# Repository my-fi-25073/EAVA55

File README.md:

# EAVA55
EAVA55 pcb &amp; qmk firmware

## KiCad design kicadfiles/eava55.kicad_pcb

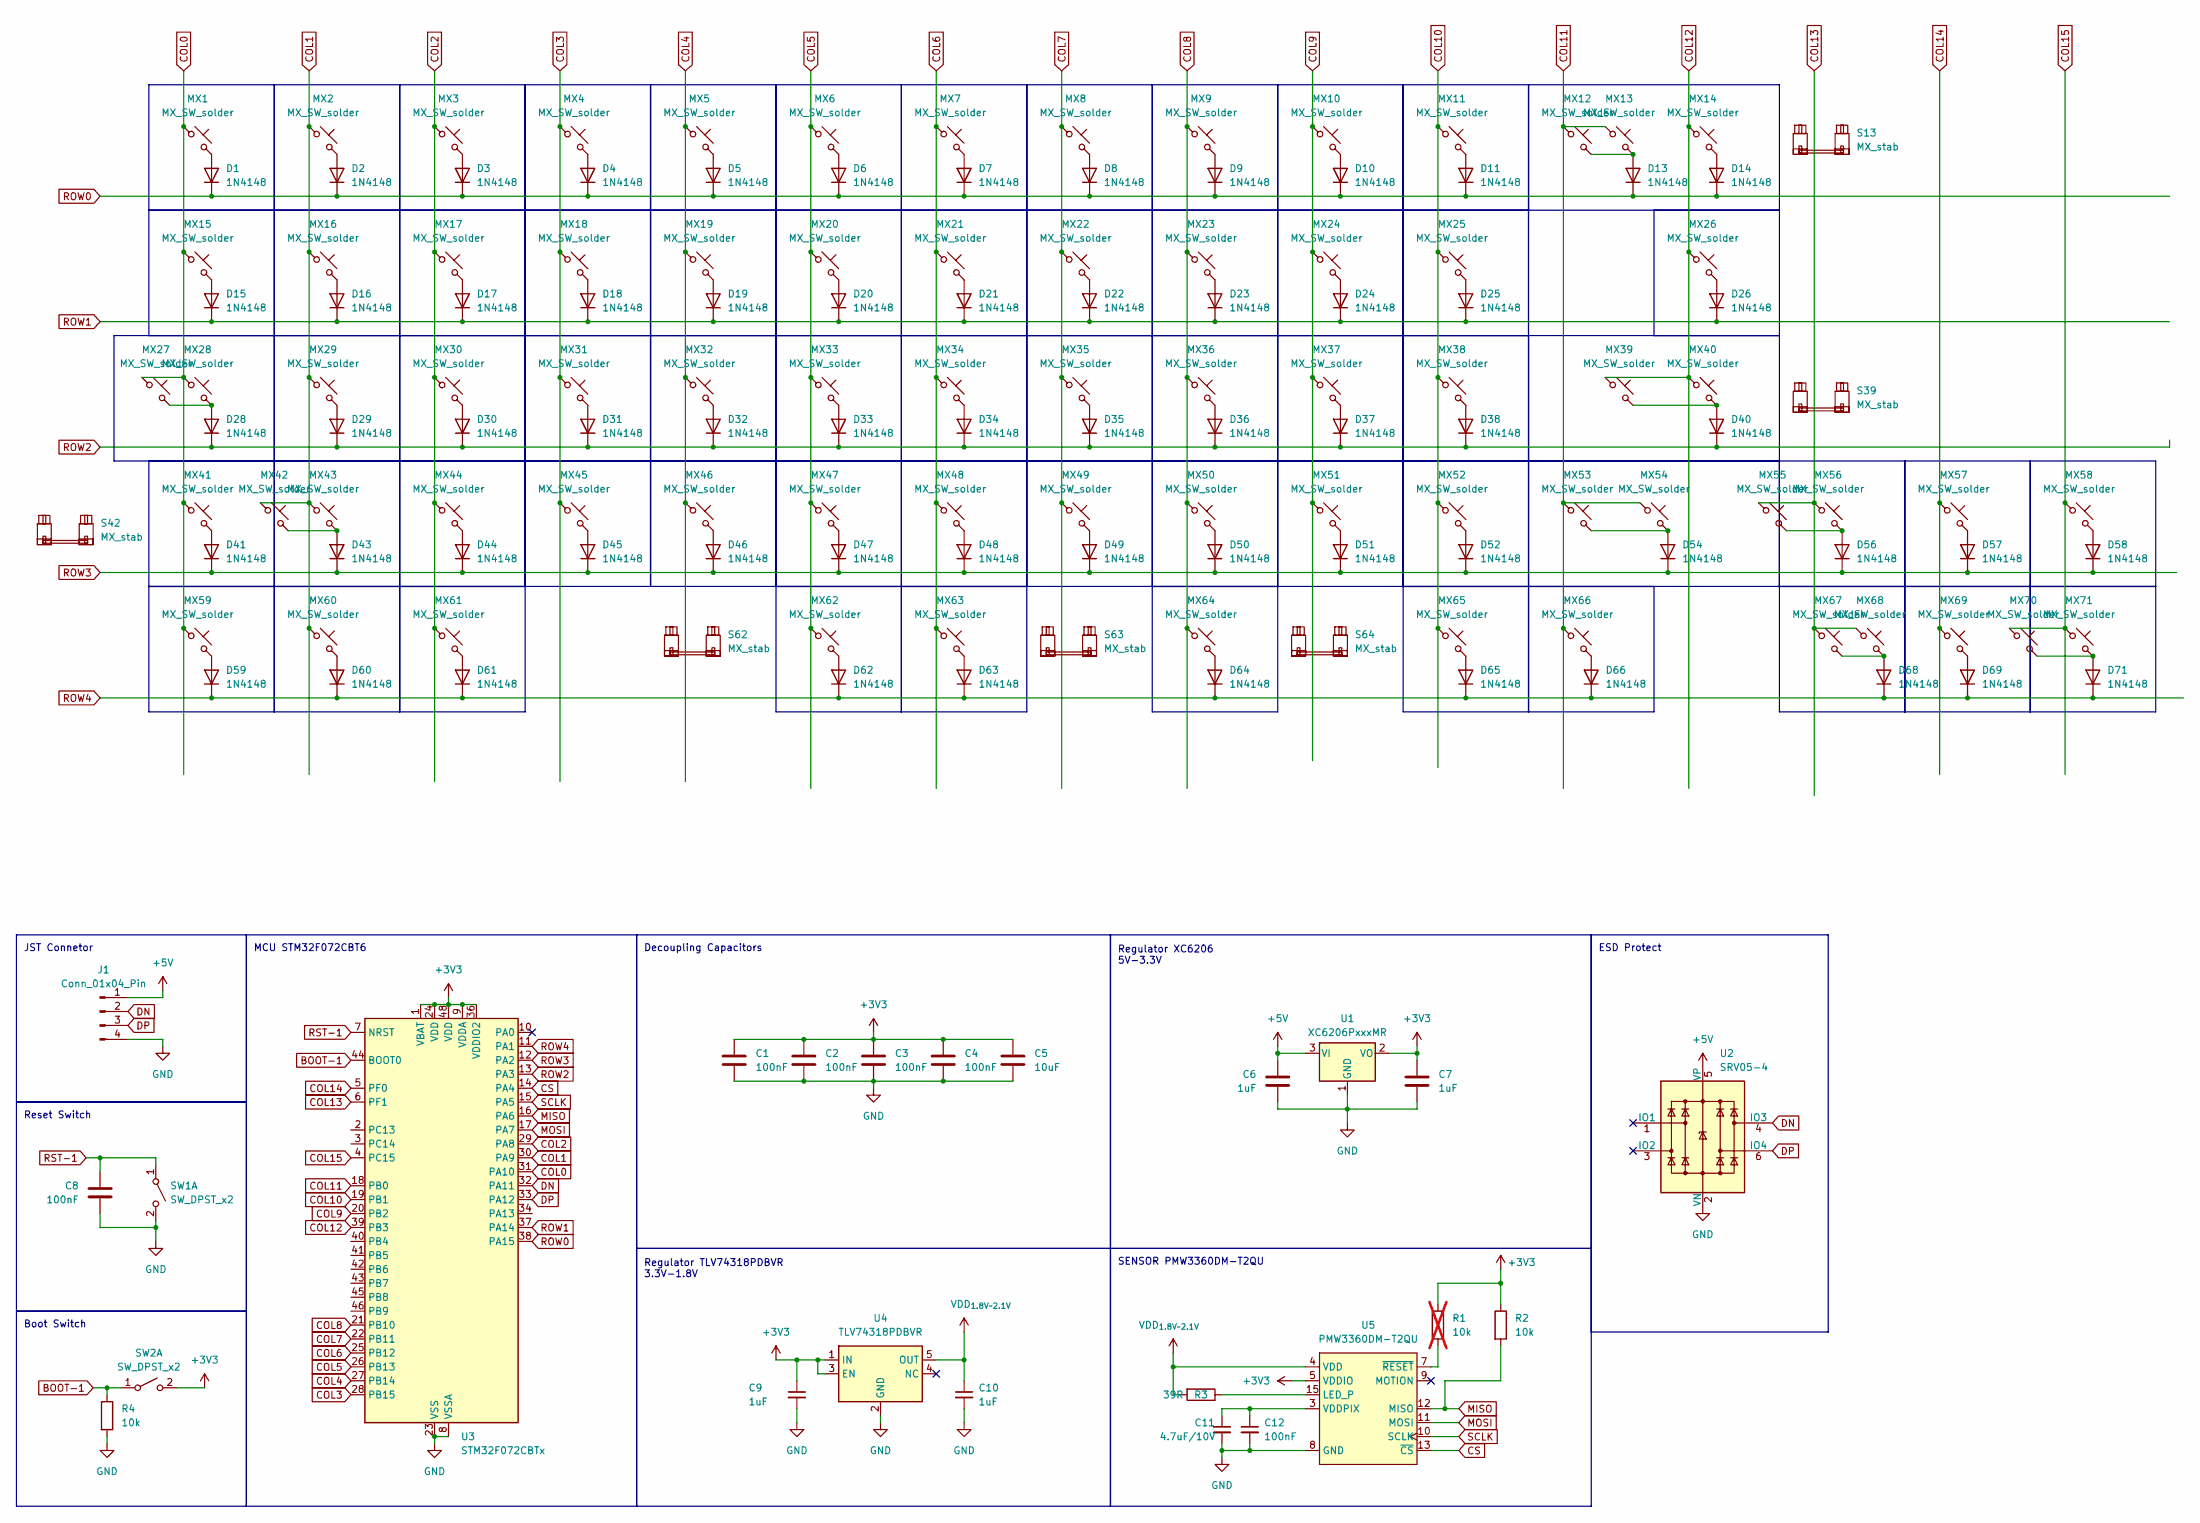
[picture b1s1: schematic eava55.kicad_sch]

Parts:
C1, C2, C3, C4, C8, C12: 100nF; C_0402_1005Metric
C5: 10uF; C_0402_1005Metric
C6, C7, C9, C10: 1uF; C_0402_1005Metric
C11: 4.7uF/10V; C_0402_1005Metric
D1, D2, D3, D4, D5, D6, D7, D8, D9, D10, D11, D13, D14, D15, D16, D17, D18, D19, D20, D21, D22, D23, D24, D25, D26, D28, D29, D30, D31, D32, D33, D34, D35, D36, D37, D38, D40, D41, D43, D44, D45, D46, D47, D48, D49, D50, D51, D52, D54, D56, D57, D58, D59, D60, D61, D62, D63, D64, D65, D66, D68, D69, D71: 1N4148; D_SOD-323_HandSoldering
J1: Conn_01x04_Pin; JST_SH_SM04B-SRSS-TB_1x04-1MP_P1.00mm_Horizontal; MPN C160404
MX1, MX2, MX3, MX4, MX5, MX6, MX7, MX8, MX9, MX10, MX11, MX12, MX13, MX14, MX16, MX17, MX18, MX19, MX20, MX21, MX22, MX23, MX24, MX25, MX29, MX30, MX31, MX32, MX33, MX34, MX35, MX36, MX37, MX38, MX39, MX41, MX42, MX44, MX45, MX46, MX47, MX48, MX49, MX50, MX51, MX52, MX53, MX56, MX57, MX58, MX60, MX62, MX63, MX64, MX66, MX67, MX69, MX71: MX_SW_solder; SW_MX_1u_tight
MX15, MX26, MX59, MX61, MX65, MX68, MX70: MX_SW_solder; SW_MX_1.5u_tight
MX27: MX_SW_solder; SW_MX_1.75u_STP_1.25_tight
MX28, MX54, MX55: MX_SW_solder; SW_MX_1.75u_tight
MX40, MX43: MX_SW_solder; SW_MX_1.25u_tight
R1: 10k; R_0805_2012Metric_Pad1.20x1.40mm_HandSolder; not fitted
R2, R4: 10k; R_0402_1005Metric
R3: 39R; R_0402_1005Metric
S13: MX_stab; STAB_MX_2u
S39, S42: MX_stab; STAB_MX_2.25u
S62, S64: MX_stab; STAB_MX_3u
S63: MX_stab; STAB_MX_6u
SW1, SW2: SW_DPST_x2; SW_Push_1P1T_XKB_TS-1187A; MPN C318884
U1: XC6206PxxxMR; SOT-23-3; MPN C5148692
U2: SRV05-4; SOT-23-6; MPN C7420376
U3: STM32F072CBTx; LQFP-48_7x7mm_P0.5mm; MPN C81720
U4: TLV74318PDBVR; SOT-23-5; MPN C485152
U5: PMW3360DM-T2QU; TrackballHolder_34mm

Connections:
+3V3: C1.1, C2.1, C3.1, C4.1, C5.1, C7.1, C9.1, R1.1, R2.1, SW2.2 (B), U1.2 (VO), U3.1 (VBAT), U3.9 (VDDA), U3.24 (VDD), U3.36 (VDDIO2), U3.48 (VDD), U4.1 (IN), U4.3 (EN), U5.5 (VDDIO)
+5V: C6.1, J1.1, U1.3 (VI), U2.5 (VP)
BOOT-1: R4.1, SW2.1 (A), U3.44 (BOOT0)
COL0: MX1.1, MX15.1, MX27.1, MX28.1, MX41.1, MX59.1, U3.31 (PA10)
COL1: MX2.1, MX16.1, MX29.1, MX42.1, MX43.1, MX60.1, U3.30 (PA9)
COL2: MX3.1, MX17.1, MX30.1, MX44.1, MX61.1, U3.29 (PA8)
COL3: MX4.1, MX18.1, MX31.1, MX45.1, U3.28 (PB15)
COL4: MX5.1, MX19.1, MX32.1, MX46.1, U3.27 (PB14)
COL5: MX6.1, MX20.1, MX33.1, MX47.1, MX62.1, U3.26 (PB13)
COL6: MX7.1, MX21.1, MX34.1, MX48.1, MX63.1, U3.25 (PB12)
COL7: MX8.1, MX22.1, MX35.1, MX49.1, U3.22 (PB11)
COL8: MX9.1, MX23.1, MX36.1, MX50.1, MX64.1, U3.21 (PB10)
COL9: MX10.1, MX24.1, MX37.1, MX51.1, U3.20 (PB2)
COL10: MX11.1, MX25.1, MX38.1, MX52.1, MX65.1, U3.19 (PB1)
COL11: MX12.1, MX13.1, MX53.1, MX54.1, MX66.1, U3.18 (PB0)
COL12: MX14.1, MX26.1, MX39.1, MX40.1, U3.39 (PB3)
COL13: MX55.1, MX56.1, MX67.1, MX68.1, U3.6 (PF1)
COL14: MX57.1, MX69.1, U3.5 (PF0)
COL15: MX58.1, MX70.1, MX71.1, U3.4 (PC15)
CS: U3.14 (PA4), U5.13 (~CS)
DN: J1.2, U2.4 (IO3), U3.32 (PA11)
DP: J1.3, U2.6 (IO4), U3.33 (PA12)
GND: C1.2, C2.2, C3.2, C4.2, C5.2, C6.2, C7.2, C8.2, C9.2, C10.2, C11.2, C12.2, J1.4, R4.2, SW1.2 (B), U1.1 (GND), U2.2 (VN), U3.8 (VSSA), U3.23 (VSS), U3.35 (VSS), U3.47 (VSS), U4.2 (GND), U5.8 (GND)
MISO: R2.2, U3.16 (PA6), U5.12 (MISO)
MOSI: U3.17 (PA7), U5.11 (MOSI)
unnamed: D1.2 (A), MX1.2
unnamed: D2.2 (A), MX2.2
unnamed: D3.2 (A), MX3.2
unnamed: D4.2 (A), MX4.2
unnamed: D5.2 (A), MX5.2
unnamed: D6.2 (A), MX6.2
unnamed: D7.2 (A), MX7.2
unnamed: D8.2 (A), MX8.2
unnamed: D9.2 (A), MX9.2
unnamed: D10.2 (A), MX10.2
unnamed: D11.2 (A), MX11.2
unnamed: D13.2 (A), MX12.2, MX13.2
unnamed: D14.2 (A), MX14.2
unnamed: D15.2 (A), MX15.2
unnamed: D16.2 (A), MX16.2
unnamed: D17.2 (A), MX17.2
unnamed: D18.2 (A), MX18.2
unnamed: D19.2 (A), MX19.2
unnamed: D20.2 (A), MX20.2
unnamed: D21.2 (A), MX21.2
unnamed: D22.2 (A), MX22.2
unnamed: D23.2 (A), MX23.2
unnamed: D24.2 (A), MX24.2
unnamed: D25.2 (A), MX25.2
unnamed: D26.2 (A), MX26.2
unnamed: D28.2 (A), MX27.2, MX28.2
unnamed: D29.2 (A), MX29.2
unnamed: D30.2 (A), MX30.2
unnamed: D31.2 (A), MX31.2
unnamed: D32.2 (A), MX32.2
unnamed: D33.2 (A), MX33.2
unnamed: D34.2 (A), MX34.2
unnamed: D35.2 (A), MX35.2
unnamed: D36.2 (A), MX36.2
unnamed: D37.2 (A), MX37.2
unnamed: D38.2 (A), MX38.2
unnamed: D40.2 (A), MX39.2, MX40.2
unnamed: D41.2 (A), MX41.2
unnamed: D43.2 (A), MX42.2, MX43.2
unnamed: D44.2 (A), MX44.2
unnamed: D45.2 (A), MX45.2
unnamed: D46.2 (A), MX46.2
unnamed: D47.2 (A), MX47.2
unnamed: D48.2 (A), MX48.2
unnamed: D49.2 (A), MX49.2
unnamed: D50.2 (A), MX50.2
unnamed: D51.2 (A), MX51.2
unnamed: D52.2 (A), MX52.2
unnamed: D54.2 (A), MX53.2, MX54.2
unnamed: D56.2 (A), MX55.2, MX56.2
unnamed: D57.2 (A), MX57.2
unnamed: D58.2 (A), MX58.2
unnamed: D59.2 (A), MX59.2
unnamed: D60.2 (A), MX60.2
unnamed: D61.2 (A), MX61.2
unnamed: D62.2 (A), MX62.2
unnamed: D63.2 (A), MX63.2
unnamed: D64.2 (A), MX64.2
unnamed: D65.2 (A), MX65.2
unnamed: D66.2 (A), MX66.2
unnamed: D68.2 (A), MX67.2, MX68.2
unnamed: D69.2 (A), MX69.2
unnamed: D71.2 (A), MX70.2, MX71.2
unnamed: R3.1, U5.15 (LED_P)
unnamed: C11.1, C12.1, U5.3 (VDDPIX)
unnamed: R1.2, U5.7 (~RESET)
ROW0: D1.1 (K), D2.1 (K), D3.1 (K), D4.1 (K), D5.1 (K), D6.1 (K), D7.1 (K), D8.1 (K), D9.1 (K), D10.1 (K), D11.1 (K), D13.1 (K), D14.1 (K), U3.38 (PA15)
ROW1: D15.1 (K), D16.1 (K), D17.1 (K), D18.1 (K), D19.1 (K), D20.1 (K), D21.1 (K), D22.1 (K), D23.1 (K), D24.1 (K), D25.1 (K), D26.1 (K), U3.37 (PA14)
ROW2: D28.1 (K), D29.1 (K), D30.1 (K), D31.1 (K), D32.1 (K), D33.1 (K), D34.1 (K), D35.1 (K), D36.1 (K), D37.1 (K), D38.1 (K), D40.1 (K), U3.13 (PA3)
ROW3: D41.1 (K), D43.1 (K), D44.1 (K), D45.1 (K), D46.1 (K), D47.1 (K), D48.1 (K), D49.1 (K), D50.1 (K), D51.1 (K), D52.1 (K), D54.1 (K), D56.1 (K), D57.1 (K), D58.1 (K), U3.12 (PA2)
ROW4: D59.1 (K), D60.1 (K), D61.1 (K), D62.1 (K), D63.1 (K), D64.1 (K), D65.1 (K), D66.1 (K), D68.1 (K), D69.1 (K), D71.1 (K), U3.11 (PA1)
RST-1: C8.1, SW1.1 (A), U3.7 (NRST)
SCLK: U3.15 (PA5), U5.10 (SCLK)
VDD_{1.8V~2.1V}: C10.1, R3.2, U4.5 (OUT), U5.4 (VDD)

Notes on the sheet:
JST Connetor
Regulator TLV74318PDBVR 3.3V-1.8V
Regulator XC6206 5V-3.3V
Decoupling Capacitors
ESD Protect
Reset Switch
SENSOR PMW3360DM-T2QU
MCU STM32F072CBT6
Boot Switch

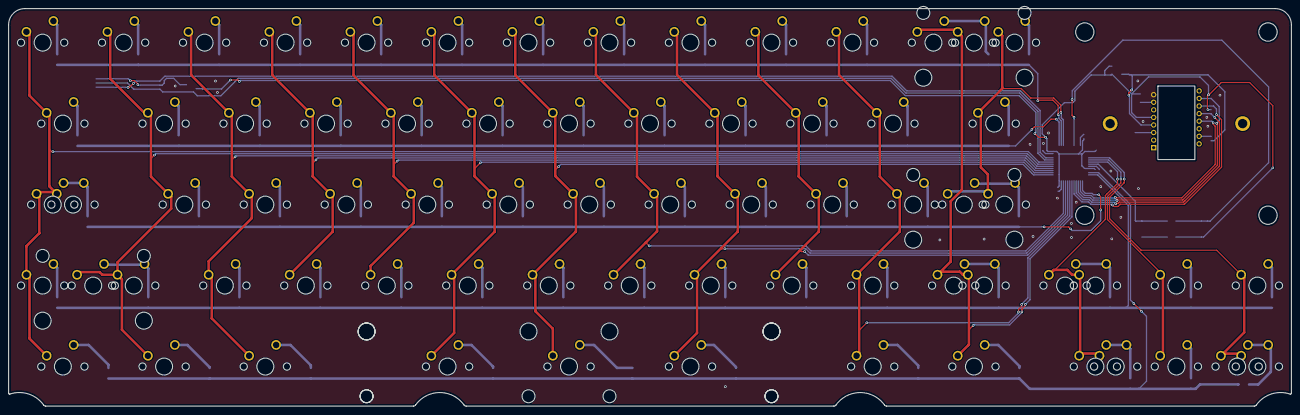
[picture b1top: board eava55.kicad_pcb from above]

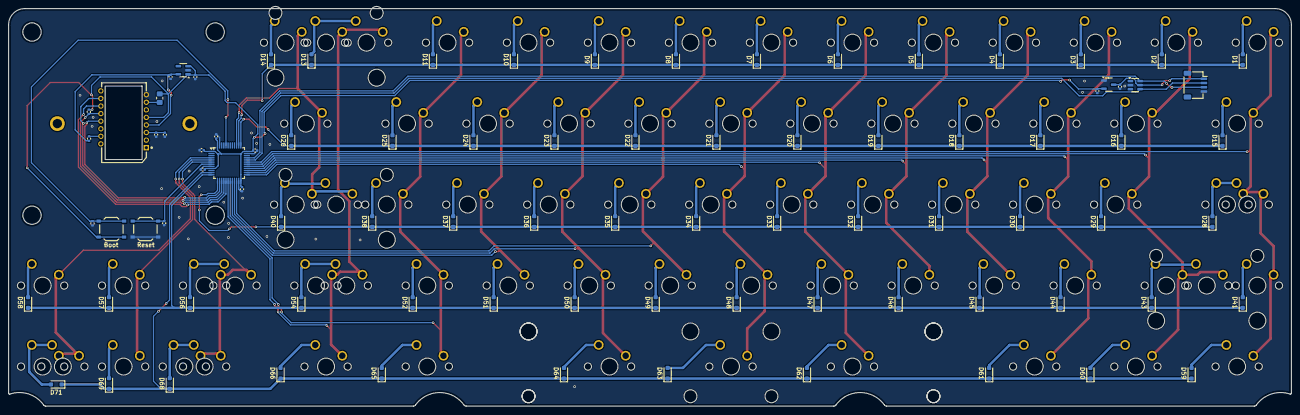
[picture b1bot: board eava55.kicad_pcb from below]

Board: 2 copper layers, 301.6 x 93.4 mm, 164 parts (86 on the bottom side), 99 nets.

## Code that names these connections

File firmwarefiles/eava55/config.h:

#pragma once

// https://docs.qmk.fm/drivers/spi
// SPI Pins for PMW3360 - STM32F072

// https://www.st.com/resource/en/datasheet/stm32f072cb.pdf
// 38 page

//  PA4 - GPIO (CS)
//  PA6 - SPI1_MISO
//  PA7 - SPI1_MOSI
//  PA5 - SPI1_SCK

#define SPI_SCK_PAL_MODE 0
#define SPI_MISO_PAL_MODE 0
#define SPI_MOSI_PAL_MODE 0

#define PMW33XX_CS_PIN A4 // SPI CS pin.
#define SPI_SCK_PIN A5
#define SPI_MISO_PIN A6
#define SPI_MOSI_PIN A7

#define DYNAMIC_KEYMAP_LAYER_COUNT 6

/* Optional. */
#define PMW33XX_CPI 800             // The CPI range is 100-12000, in increments of 100. Defaults to 1600 CPI.
#define PMW33XX_CLOCK_SPEED 2000000 // Sets the clock speed that the sensor runs at. Defaults to 2000000
#define MOUSE_EXTENDED_REPORT       // Use -32767 to 32767, instead of just -127 to 127.
#define WHEEL_EXTENDED_REPORT       // Use -32767 to 32767, instead of just -127 to 127.

#define USB_POLLING_INTERVAL_MS 1

#define PMW33XX_SPI_DIVISOR 64
#define POINTING_DEVICE_TASK_THROTTLE_MS 2
#define FORCE_NKRO
#define POINTING_DEVICE_INVERT_Y
// https://docs.qmk.fm/features/pointing_device

// Addintion GPIO Pins for keyboard

// ADD0 - F1
// ADD1 - F0
// ADD2 - A0
// ADD3 - C15
// ADD4 - A1
// ADD5 - C14
// ADD6 - A2
// ADD7 - C13

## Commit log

2025-06-22 Added kicad files!
2025-06-23 updated pcb edge cut
2025-07-20 Updated files
